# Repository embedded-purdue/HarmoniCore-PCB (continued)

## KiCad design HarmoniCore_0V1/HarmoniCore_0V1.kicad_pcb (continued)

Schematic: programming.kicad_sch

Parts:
C701, C702, C703, C704, C705, C706, C707, C709, C711, C712, C714, C717: 0u1; C_0603
C708: 10u; C_0603
C710, C713, C715: 10u; C_0603; not fitted
C716: 47u; C_1210
FB701, FB702: FB600R_0603; BEADC1608X95N
LED1: LTST-C170GKT; LED_0805
R1, R2, R3, R716: 4k7; R_0603
R4, R710, R711, R712, R713: 100; R_0603
R5: 49.9; R_0603
R701, R702: 10k; R_0603
R703, R704, R705, R707: 22; R_0603
R706: 2k; R_0603
R714, R715: 1k8; R_0603
SW701: SW_Push; SMD_F260QG_EWI-L
TP7: 5000; KEYSTONE_5001; PARTREV H
TP8: 5001; KEYSTONE_5001; PARTREV H
U401: XC7A25T-CSG325; Xilinx_CSG325
U701: FT232HL-REEL; LQFP48_FT232HL_FTD-L
U702: 93LC56B-I_SN; SOIC127P599X175-8N
U703: S25FL128SAGMFI000; SO3016_INF-L

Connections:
12M_FTDI: U701.1 (OSCI); also elsewhere on the board
+3V3D: C716.1, C717.1, R1.2, R2.2, R3.2, R4.2, R714.2, R715.2, R716.2, U401.E10 (VCCO_0), U401.R10 (VCCO_0), U703.2 (VCC); also elsewhere on the board
+3V3_FTDI: C704.1, C705.1, C706.1, C707.1, C708.1, C711.1, FB701.1, FB702.1, R701.2, TP7.TP, U701.12 (VCCIO), U701.24 (VCCIO), U701.39 (VCCD), U701.46 (VCCIO), U702.8 (VCC)
+VCORE: C701.1, U701.38 (VCORE)
D_N: U701.6 (DM); also elsewhere on the board
D_P: U701.7 (DP); also elsewhere on the board
Earth: C701.2, C702.2, C703.2, C704.2, C705.2, C706.2, C707.2, C708.2, C709.2, C710.2, C711.2, C712.2, C713.2, C714.2, C715.2, C716.2, C717.2, R5.2, R702.1, SW701.2, TP8.TP, U401.K9 (VREFN_0), U401.K10 (VP_0), U401.L9 (VN_0), U401.L10 (VREFP_0), U401.M9 (DXN_0), U401.M10 (DXP_0), U701.4 (AGND), U701.9 (AGND), U701.10 (GND), U701.11 (GND), U701.22 (GND), U701.23 (GND), U701.35 (GND), U701.36 (GND), U701.41 (AGND), U701.42 (TEST), U701.47 (GND), U701.48 (GND), U702.5 (VSS), U703.10 (VSS); also elsewhere on the board
M0: U401.R12 (M0_0); also elsewhere on the board
M1: U401.R11 (M1_0); also elsewhere on the board
M2: U401.F13 (M2_0); also elsewhere on the board
unnamed: LED1.1, R5.1
unnamed: R3.1, U401.E12 (CFGBVS_0)
unnamed: LED1.2, R4.1, U401.F12 (DONE_0)
unnamed: R1.1, U401.T10 (INIT_B_0)
unnamed: R2.1, SW701.1, U401.P10 (PROGRAM_B_0)
unnamed: R703.1, U701.13 (ADBUS0)
unnamed: R704.1, U701.14 (ADBUS1)
unnamed: R705.1, U701.15 (ADBUS2)
unnamed: R707.1, U701.16 (ADBUS3)
unnamed: U701.44 (EECLK), U702.2 (CLK)
unnamed: U701.45 (EECS), U702.1 (CS)
unnamed: R706.1, U701.43 (EEDATA), U702.3 (DI)
unnamed: R702.2, U701.5 (REF)
unnamed: C702.1, R701.1, U701.34 (RESET#)
unnamed: C703.1, U701.37 (VCCA)
unnamed: R706.2, U702.4 (DO)
unnamed: R713.2, R715.1, U703.1 (HOLD#/IO3)
unnamed: R710.2, U703.15 (SI/IO0)
unnamed: R711.2, U703.8 (SO/IO1)
unnamed: R712.2, R714.1, U703.9 (WP#/IO2)
QSPI_CLK: U401.E8 (CCLK_0), U703.16 (SCK); also elsewhere on the board
QSPI_CS: R716.1, U703.7 (CS#); also elsewhere on the board
QSPI_DO0: R710.1; also elsewhere on the board
QSPI_DO1: R711.1; also elsewhere on the board
QSPI_DO2: R712.1; also elsewhere on the board
QSPI_DO3: R713.1; also elsewhere on the board
TCK: R703.2, U401.R8 (TMS_0); also elsewhere on the board
TDI: R704.2, U401.T9 (TDI_0); also elsewhere on the board
TDO: R705.2, U401.T8 (TDO_0); also elsewhere on the board
TMS: R707.2, U401.F8 (TCK_0); also elsewhere on the board
VBUS: C709.1, C710.1, U701.40 (VREG); also elsewhere on the board
VPHY_FTDI: C712.1, C713.1, FB701.2, U701.3 (VPHY)
VPLL_FTDI: C714.1, C715.1, FB702.2, U701.8 (VPLL)

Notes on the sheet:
Test Points
[${#}] ${TITLE}
QSPI-Flash
USB-JTAG Bridge
GLOBAL NETS

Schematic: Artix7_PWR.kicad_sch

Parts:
C401, C402, C421, C424: 100u; C_1210
C403, C404, C406, C407, C417, C422, C423, C426, C428: 4u7; C_0805; Part Number GRM21BR71A475KA73K; DigiKey Part Number 490-6479-2-ND
C405, C420: 47u; C_1210
C408, C409, C410, C411, C412, C413, C414, C415, C416, C418, C419, C425, C427, C429, C430, C431, C432, C433: 0.47u; C_0603
R8: 100; R_0603
U401: XC7A25T-CSG325; Xilinx_CSG325

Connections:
+1V0D: C405.1, C408.1, C424.1, C426.1, C428.1, C430.1, C432.1, C433.1, U401.F7 (VCCINT), U401.F9 (VCCINT), U401.F11 (VCCBRAM), U401.G8 (VCCINT), U401.G10 (VCCBRAM), U401.H7 (VCCINT), U401.H9 (VCCINT), U401.H11 (VCCBRAM), U401.J8 (VCCINT), U401.J12 (VCCINT), U401.K7 (VCCINT), U401.K11 (VCCINT), U401.L8 (VCCINT), U401.L12 (VCCINT), U401.M7 (VCCINT), U401.M11 (VCCINT), U401.N8 (VCCINT), U401.N10 (VCCINT), U401.N12 (VCCINT), U401.P9 (VCCINT), U401.P11 (VCCINT); also elsewhere on the board
+1V8D: C411.1, C414.1, C417.1, C420.1, U401.G12 (VCCAUX), U401.H13 (VCCAUX), U401.K13 (VCCAUX), U401.M13 (VCCAUX), U401.P13 (VCCAUX); also elsewhere on the board
+3V3D: C401.1, C402.1, C403.1, C404.1, C406.1, C407.1, C409.1, C410.1, C412.1, C413.1, C415.1, C416.1, C418.1, C419.1, C421.1, C422.1, C423.1, C425.1, C427.1, C429.1, C431.1, U401.A16 (VCCO_15), U401.B13 (VCCO_15), U401.C10 (VCCO_15), U401.D17 (VCCO_15), U401.E14 (VCCO_15), U401.G18 (VCCO_15), U401.H15 (VCCO_15), U401.L6 (VCCO_34), U401.L16 (VCCO_14), U401.M3 (VCCO_34), U401.P7 (VCCO_34), U401.P17 (VCCO_14), U401.R4 (VCCO_34), U401.R14 (VCCO_14), U401.T1 (VCCO_34), U401.T11 (VCCO_14), U401.U8 (VCCO_14), U401.U18 (VCCO_14), U401.V5 (VCCO_34), U401.V15 (VCCO_14); also elsewhere on the board
Earth: C401.2, C402.2, C403.2, C404.2, C405.2, C406.2, C407.2, C408.2, C409.2, C410.2, C411.2, C412.2, C413.2, C414.2, C415.2, C416.2, C417.2, C418.2, C419.2, C420.2, C421.2, C422.2, C423.2, C424.2, C425.2, C426.2, C427.2, C428.2, C429.2, C430.2, C431.2, C432.2, C433.2, R8.2, U401.A1 (GND), U401.A2 (MGTAVTT), U401.A3 (MGTPRXN1_216), U401.A4 (MGTPRXP1_216), U401.A5 (GND), U401.A7 (GND), U401.A8 (GND), U401.A11 (GND), U401.A18 (GND), U401.B3 (GND), U401.B4 (MGTAVCC), U401.B7 (GND), U401.B8 (GND), U401.B18 (GND), U401.C1 (MGTAVTT), U401.C2 (GND), U401.C3 (MGTPRXN2_216), U401.C4 (MGTPRXP2_216), U401.C5 (MGTAVCC), U401.C6 (GND), U401.C7 (GND), U401.C15 (GND), U401.D3 (GND), U401.D4 (GND), U401.D7 (GND), U401.D12 (GND), U401.E1 (MGTAVTT), U401.E2 (GND), U401.E3 (MGTPRXN0_216), U401.E4 (MGTPRXP0_216), U401.E5 (MGTAVCC), U401.E6 (GND), U401.E7 (GND), U401.E9 (GND), U401.F3 (MGTAVTT), U401.F4 (GND), U401.F5 (MGTAVCC), U401.F6 (GND), U401.F10 (GND), U401.F16 (GND), U401.G1 (GND), U401.G2 (MGTAVTT), U401.G3 (MGTPRXN3_216), U401.G4 (MGTPRXP3_216), U401.G5 (GND), U401.G6 (GND), U401.G7 (GND), U401.G9 (GND), U401.G11 (GND), U401.G13 (GND), U401.H3 (GND), U401.H4 (GND), U401.H5 (GND), U401.H6 (GND), U401.H8 (GND), U401.H10 (GND), U401.H12 (GND), U401.J1 (GND), U401.J2 (GND), U401.J3 (GND), U401.J7 (GND), U401.J11 (GND), U401.J13 (GND), U401.J17 (GND), U401.K4 (GND), U401.K8 (GND), U401.K12 (GND), U401.K14 (GND), U401.L1 (GND), U401.L7 (GND), U401.L11 (GND), U401.L13 (GND), U401.M8 (GND), U401.M12 (GND), U401.M18 (GND), U401.N5 (GND), U401.N7 (GND), U401.N9 (GND), U401.N11 (GND), U401.N13 (GND), U401.N15 (GND), U401.P2 (GND), U401.P8 (GND), U401.P12 (GND), U401.R9 (GND), U401.T6 (GND), U401.T16 (GND), U401.U3 (GND), U401.U13 (GND), U401.V1 (GND), U401.V10 (GND), U401.V18 (GND); also elsewhere on the board
unnamed: R8.1, U401.A6 (MGTRREF_216)

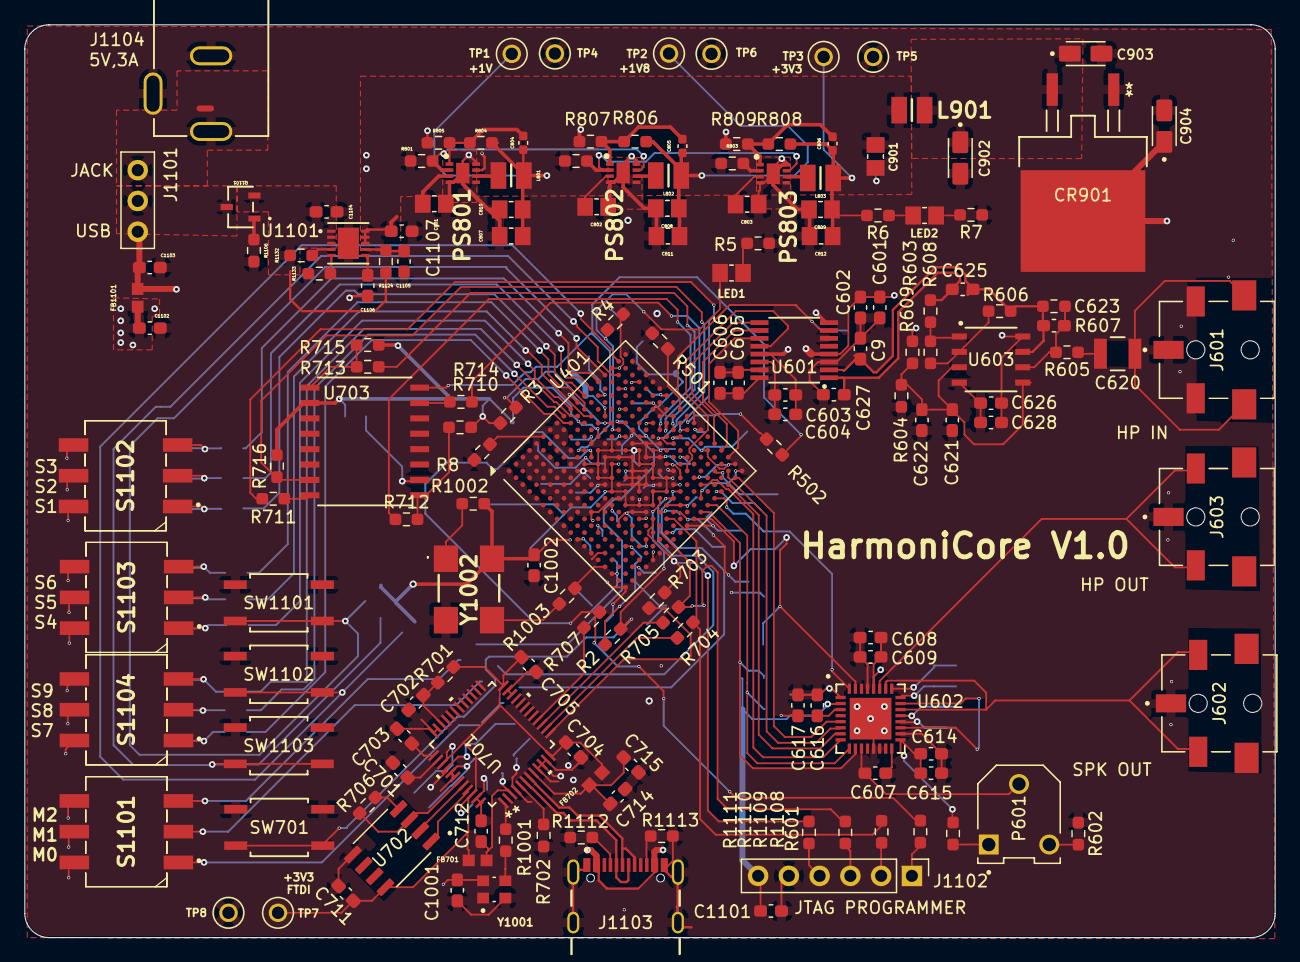
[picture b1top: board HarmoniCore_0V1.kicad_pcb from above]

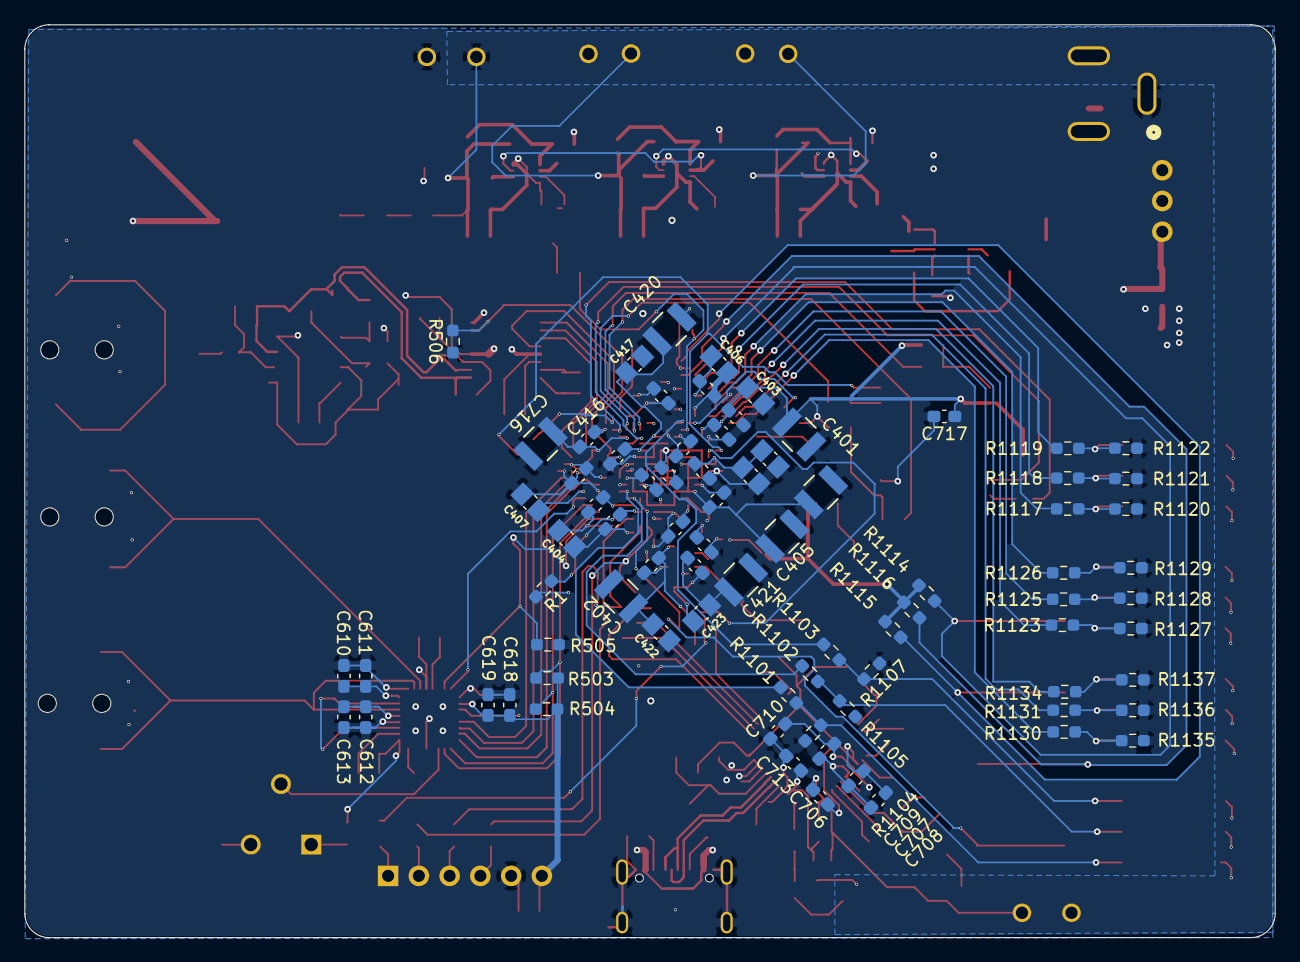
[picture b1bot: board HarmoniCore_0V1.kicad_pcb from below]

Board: 6 copper layers, 103.3 x 75.4 mm, 237 parts (79 on the bottom side), 133 nets.

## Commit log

2025-09-21 Initial Commit : Adding template for KiCAD project
2025-09-21 Inital Commit: Added sample documentation
2025-09-21 Documentation: Added requirements and finished setting up #1
2025-09-24 Documentation: Adding some User Guides (UG) and reference design info
2025-09-28 ADC spec sheet
2025-09-30 Documentation : Added Programming pins info
2025-09-30 Documentation : Changed name of ADC
2025-10-02 library files for dac/adc
2025-10-05 documentation for dac
2025-10-05 Added ASCII Pinout file and a table for the programming pins
2025-10-05 template for dac and adc schematic
2025-10-05 Added FT232 Docs
2025-10-19 Libraries : Added XILINX Symbol
2025-10-19 Adding XILINX
2025-10-19 Added VCK190 XTP610 reference schematic (see page 25)
2025-10-19 Hardware : Added pinout
2025-11-02 Docs: Added ZETTBRETT
2025-11-02 Symbol: added FTDI chip
2025-11-02 Symbol: added ECS 2520MV 120 BN TR
2025-11-02 dac work p1
2025-11-02 Schematic: started Programming schematic
2025-11-02 DAC done
2025-11-02 hopefully mostly done analog front end
2025-11-09 i2c documentation and clean up
2025-11-09 Added power electronics IC
2025-11-16 Started programming schematic
2025-11-16 ic verification
2025-11-30 added 1V0D symbol and digital power converters
2025-11-30 added IC footprints and more designer notes on calculations for digital
2025-12-02 added part numbers, added symbols and footprints to libraries, overall power changes
2025-12-02 deleted stuff restored
2025-12-02 Renumbering for parts
2025-12-02 Changed 22uF symbol
2025-12-02 Updated schematic 22uF
2025-12-02 Got rid of unused analog PE
2025-12-04 Kicad Error corrections
2025-12-05 HW: Added ARTIX 7 and corrected some schematics
2025-12-05 Fixed some PE
2025-12-05 PE: Added decoupling caps requirements
2025-12-06 resitors PE
2025-12-07 updated pe
2025-12-07 analog page
2025-12-07 HW: PE added components and fixed lib
2025-12-07 Symbols: Added 22 ohm 0603 resistor
2025-12-08 psuh to be safe
2025-12-08 HW: Decoupling caps on Artix 7 and Modified Artix 7 symb
2025-12-08 HW: Loadded PCB just to try
2025-12-10 op amp computations
2025-12-17 HW: Added some oscillators and such
2025-12-17 HW: Halfway done on programming FTDI, need to add EEPROM
2025-12-18 HW: Finished drafted of FTDI Schematic
2025-12-24 HW: half way done with QSPI Flash
2025-12-26 HW: QSPI Flash should be done
2025-12-26 HW: Programming page DONE and some STEP Files corrected
2025-12-28 HW: Added USB-C, and Dipswitch for boot mode selection
2025-12-31 HW: Added DC Jack and eFuse. Need to add protection circuitry for Power Input
2025-12-31 HW: Tried to comppile BOM
2026-01-01 HW: Added USB Protection and Power supply protection
2026-01-01 HW: Minor change
2026-01-04 HW: Added JTAG header
2026-01-06 HW: Added some buttons for user input
2026-01-06 HW: Added some FPGA IOs
2026-01-12 HW: Added the Analog front end to the FPGA (arbitrary pins)
2026-01-25 Requirements for JLCPCB
2026-01-25 HW: DRAWIO FOR LAYOUT ADDED
2026-02-01 Started Layout
2026-02-01 Symbols: add Green LED. Programming: minor changes.
2026-02-01 Symbols: Add green LED footprint and model
2026-02-01 Fixed green LED footprint
2026-02-03 Layout: Modified some constraints to match Kicad and added a test VIA on the FPGA
2026-02-08 PE Digital: added 3v3D indicator diode
2026-02-08 DRC Update
2026-02-08 DRC Update V2
2026-02-08 Added Documentation
2026-02-08 Symbols: Added Red and Black TPs
2026-02-08 Digital PE: Added indicator diode and test points
2026-02-08 Added Oscilloscope Reading for Microphone Test
2026-02-08 Programming: Added 3v3FTDI TPs
2026-02-08 Layout
2026-02-15 Added Tranceiver Power connections
2026-02-15 Added LDO
2026-02-15 HW: Decoupling for ADC and DAC placed
2026-02-15 HW: Set TP as DNP
2026-02-15 preamp for adc
2026-02-16 HW: Pretify opamp schm
2026-02-16 HW: Misc
2026-02-22 LAYOUT: Routed ADC and DAC Analog (prelim)
2026-02-22 pi filter and LDO
2026-02-22 fixes to the library related to ui
2026-02-22 [User Input] Added more input switches for S10-S12
2026-02-22 alternative resister values + board update
2026-02-22 Output jacks
2026-02-22 Speaker Output Pin 1 Changed
    0 Ohm Resistor Jumpers Added to Pin 1 and connected to SPKM
2026-02-22 [User Input] Flipped protection diode
2026-02-23 LAYOUT: Routed PE, next is decoupling caps
2026-02-23 added 4.7 uF tantalum cap
2026-03-01 DOG BONE FAN-OUT
2026-03-01 STARTED PLACING DECOUPLING BUT MAYBE WILL RE-DO
2026-03-01 CORRECTED ANALOG
2026-03-01 MEETING 03/01
2026-03-02 Routing
2026-03-03 Layout routing
2026-03-03 More layout
2026-03-05 MORE ROUTING!
2026-03-08 SCHM UPDATE
2026-03-08 not much
2026-03-22 SOME ROUTING FOR USER INPUT
2026-03-22 Done draft PCB
2026-03-29 Getting ready for order
2026-03-29 Digikey BOM
    added Digikey BOM to Assembly
2026-03-29 Added LCSC BOM and BOM todo .txt file
2026-03-29 Added recent PDF
2026-03-29 Added one board digikey BOM to assesmbly
2026-03-30 Production files
2026-04-07 Kicad 10!
2026-04-07 Kicad 10! !
2026-04-07 Not save history
2026-04-07 Not save hisotry 2
2026-04-07 Final gitignore?
2026-04-07 Stop tracking KiCad .history folder
2026-04-12 ADDING ASSEMBLY FILES
2026-04-15 Getting manufacturing ready!
